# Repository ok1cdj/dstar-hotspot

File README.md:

# DSTAR-Hotspot with Arduino RPi.
D-STAR hotspot with open HW and SW under GNU GPL2 based on
DV-MEGA - by Guus van Dooren (PE1PLM) and [DVSP2](http://tech4.pl/SQ9MDD/?p=92) by SQ9MDD.

Tested with Raspberry PI 2 and [Western D-STAR image](http://www.westerndstar.co.uk/html/downloads.html).

## TODO

* add partlist
* add more info about HW and building
* add gerber files for production
* add configuration for Ircddbgateway and D-STAR repeater

## How to compile SW for Arduino

Use Arduino 1.5.X

Before programming Arduino be sure the "HardwareSerial.cpp" under Arduino instalation folder\hardware\arduino\cores\arduino is changed.

From:
```
#if (RAMEND < 1000)
#define SERIAL_BUFFER_SIZE 16
#else
#define SERIAL_BUFFER_SIZE 64
#endif
```

To:
```
#if (RAMEND < 1000)
#define SERIAL_BUFFER_SIZE 16
#else
#define SERIAL_BUFFER_SIZE 128
#endif

```
## HOW to remove console from serial on RPi

$ sudo nano /boot/cmdline.txt

From:
```
　GNU nano 2.2.6　　　　　　　　　　File: /boot/cmdline.txt
dwc_otg.lpm_enable=0 console=ttyAMA0,115200 console=tty1 root=/dev/mmcblk0p2 rootfstype=ext4 elevator=deadline rootwait 
```
To:
```
dwc_otg.lpm_enable=0 rpitestmode=1 console=tty1 root=/dev/mmcblk0p2 rootfstype=ext4 elevator=deadline rootwait
```

$ sudo nano /etc/inittab

From:
```
　GNU nano 2.2.6　　　　　　　　　　File: /etc/inittab
#Spawn a getty on Raspberry Pi serial line
T0:23:respawn:/sbin/getty -L ttyAMA0 115200 vt100
```
To:
```
#T0:23:respawn:/sbin/getty -L ttyAMA0 115200 vt100
```

## You need configure Ircddbgateway and D-STAR repeater package  to run hotspot

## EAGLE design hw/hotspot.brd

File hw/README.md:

# dstar-hotspot
Schematic and PCB files for EAGLE 6.X.

Acrylic (3 mm) case in DXF format for laser cutter.

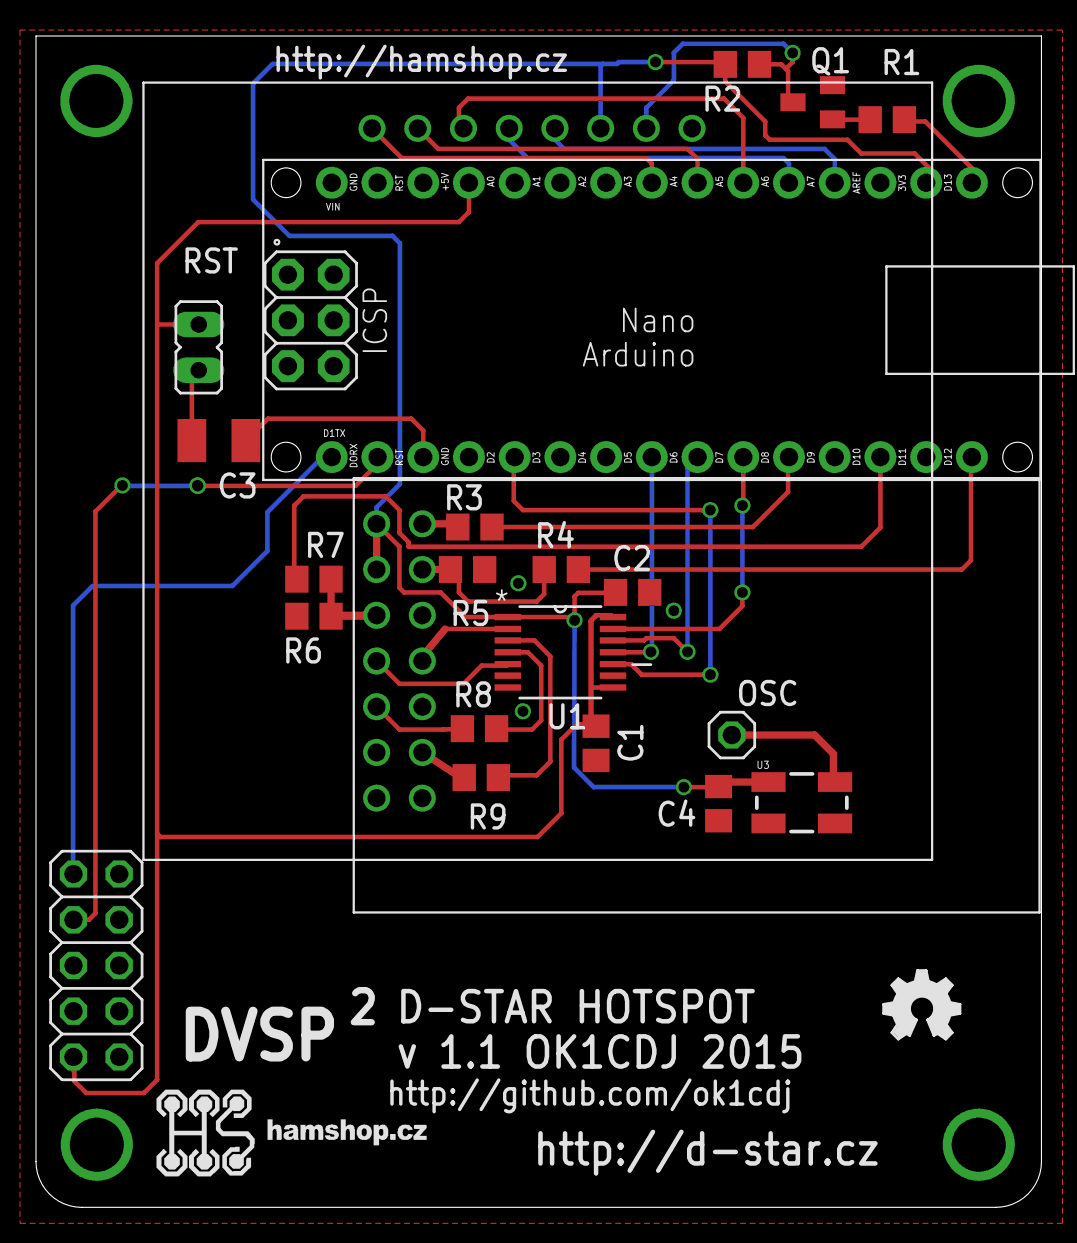
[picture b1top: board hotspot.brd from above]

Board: 2 copper layers, 55.9 x 65.1 mm, 23 parts (0 on the bottom side), 32 nets.

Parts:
C1, C2: C0805
C3: 10uF; SMC_B
C4: 100nF; C0805
LCD1: N5110-BRDOPOS; PH-7366-BRD-0-NOFRAME
LOGO1: OSHW_LOGO_FILLX0150-NT; OSHW_FILLX150_NOTEXT
OSC: 1X01
PCB1: ARDUINO_NANO
Q1: BC847; SOT23
R1, R8, R9: 1k; R0805
R2: 10k; R0805
R3: 2k2; R0805
R4, R7: 1k5; R0805
R5, R6: 3k3; R0805
RPI: 2X05
RST: JP1
U1: TXB0104PWR; SOP65P640X120-14N
U3: OSCILLATOR5X3; CRYSTAL-SMD-5X3
U$1: RF7021SE; B-RF7021SE

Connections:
3V3: C2.1, C4.1, LCD1.VCC, PCB1.3V3, R2.2, U1.1, U3.4, U$1.P$1, U$1.P$3
5V: C1.1, PCB1.5V, RPI.2, RST.2, U1.8, U1.14
GND: C1.2, C2.2, C4.2, LCD1.GND, PCB1.GND, PCB1.GND., Q1.2, R5.1, R6.2, RPI.6, RPI.9, U1.7, U3.2, U$1.P$13, U$1.P$14
unnamed: LCD1.RST, PCB1.A4
unnamed: LCD1.CE, PCB1.A3
unnamed: LCD1.DC, PCB1.A2
unnamed: LCD1.DIN, PCB1.A1
unnamed: LCD1.CLK, PCB1.A0
unnamed: R4.2, R5.2, U$1.P$4
unnamed: LCD1.LIGHT, Q1.3, R2.1
unnamed: Q1.1, R1.1
unnamed: PCB1.D13, R1.2
unnamed: R3.2, U$1.P$2
unnamed: PCB1.D8, R3.1
unnamed: PCB1.D12, R4.1
unnamed: PCB1.D7, U1.13
unnamed: PCB1.D2, U1.10
unnamed: PCB1.D5, U1.11
unnamed: PCB1.D6, U1.12
unnamed: R6.1, R7.2, U$1.P$5
unnamed: PCB1.D10, R7.1
unnamed: R8.2, U$1.P$9
unnamed: R8.1, U1.4
unnamed: U1.2, U$1.P$8
unnamed: U1.5, U$1.P$7
unnamed: R9.2, U1.3
unnamed: C3.-, RST.1
unnamed: OSC.1, U3.3
unnamed: PCB1.RX1, RPI.8
unnamed: R9.1, U$1.P$12
unnamed: PCB1.TX1, RPI.10
unnamed: C3.+, PCB1.RST

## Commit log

2015-10-08 First batch of files
2015-10-08 Changes in readme
2015-10-08 Added SW for arduino
